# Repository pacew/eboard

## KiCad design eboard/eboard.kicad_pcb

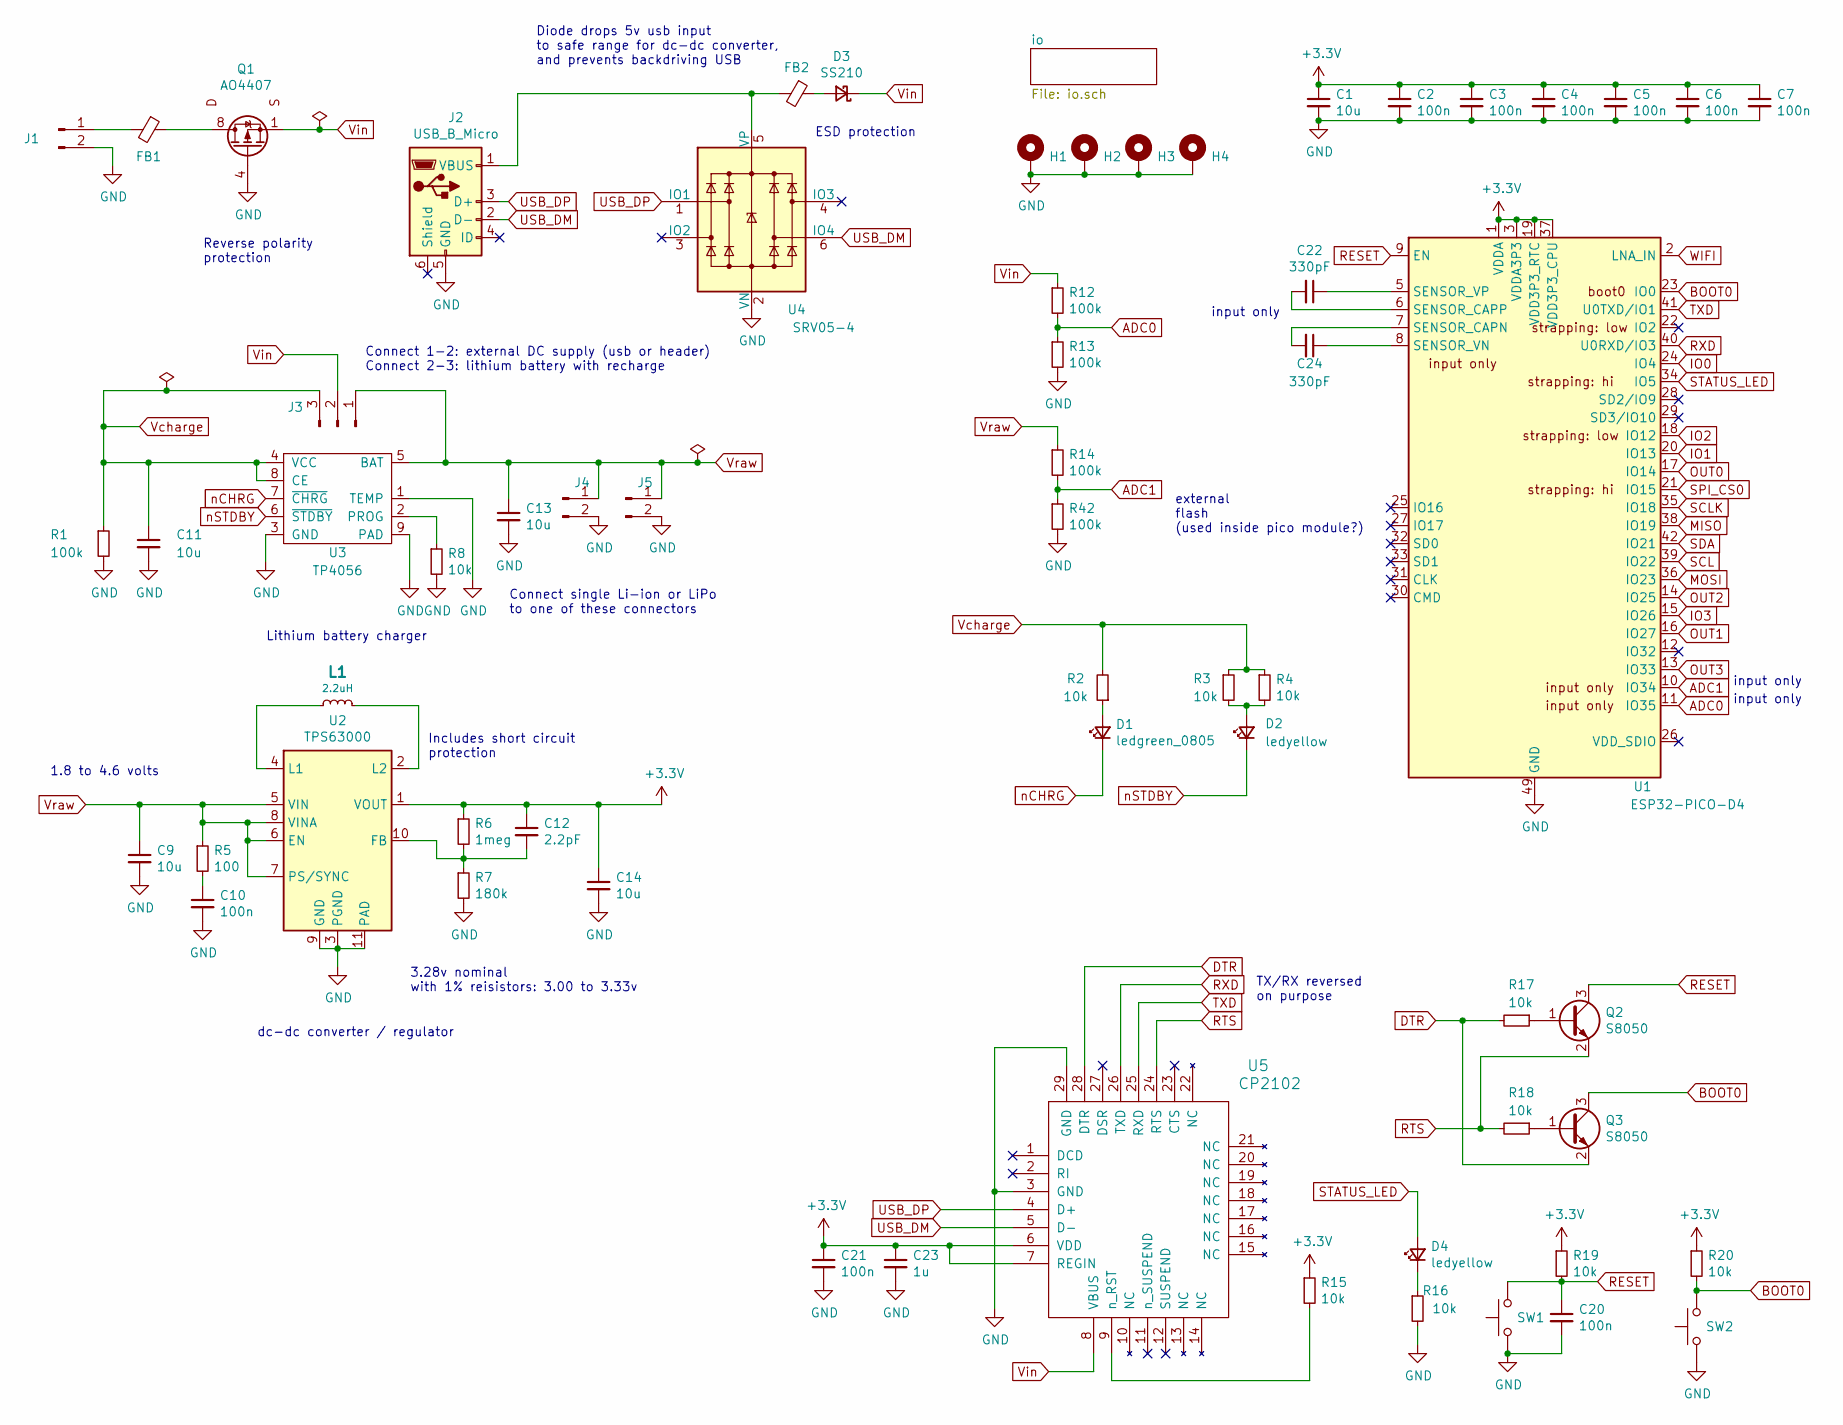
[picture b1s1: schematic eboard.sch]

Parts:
C1, C9, C11, C13, C14: 10u; C_0402_1005Metric; LCSC C15525
C2, C3, C4, C5, C6, C7, C10, C20, C21: 100n; C_0402_1005Metric; LCSC C1525
C12: 2.2pF; C_0402_1005Metric; LCSC C1559
C22, C24: 330pF; C_0402_1005Metric; LCSC C13533
C23: 1u; C_0402_1005Metric; LCSC C52923
D1: ledgreen_0805; LED_0805_2012Metric; LCSC C2297
D2, D4: ledyellow; LED_0603_1608Metric; LCSC C72038
D3: SS210; D_SMA; LCSC C14996
FB1, FB2: bead; L_0805_2012Metric; LCSC C1015
H1, H2, H3, H4: MountingHole_Pad; MountingHole_3.2mm_M3_Pad
J1, J5: Conn_01x02_Male; PinHeader_1x02_P2.54mm_Vertical
J2: USB_B_Micro; USB_Micro-B_Molex-105017-0001
J3: Conn_01x03_Male; PinHeader_1x03_P2.54mm_Vertical
J4: jst_battery; JST_PH_B2B-PH-K_1x02_P2.00mm_Vertical
L1: 2.2uH; L_Coilcraft_XxL4020; LCSC C167747
Q1: AO4407; SOIC-8_3.9x4.9mm_P1.27mm; LCSC C469397
Q2, Q3: S8050; SOT-23; LCSC C2146
R1, R12, R13, R14, R42: 100k; R_0402_1005Metric; LCSC C25741
R2, R3, R4, R8, R15, R16, R17, R18, R19, R20: 10k; R_0402_1005Metric; LCSC C25744
R5: 100; R_0402_1005Metric; LCSC C25076
R6: 1meg; R_0603_1608Metric; LCSC C22935
R7: 180k; R_0603_1608Metric; LCSC C22827
SW1, SW2: pushbutton_switch; SW_PUSH_6mm
U1: ESP32-PICO-D4; QFN-48-1EP_7x7mm_P0.5mm_EP5.3x5.3mm; LCSC C193707
U2: TPS63000; Texas_DRC0010J_ThermalVias; LCSC C24966
U3: TP4056; SOIC-8-1EP_3.9x4.9mm_P1.27mm_EP2.29x3mm_ThermalVias; LCSC C16581
U4: SRV05-4; SOT-23-6; LCSC C85364
U5: CP2102; QFN-28-1EP_5x5mm_P0.5mm_EP3.35x3.35mm_ThermalVias; LCSC C6568

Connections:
+3V3: C1.1, C2.1, C3.1, C4.1, C5.1, C6.1, C7.1, C12.1, C14.1, C21.1, C23.1, R6.1, R15.1, R19.1, R20.1, U1.1 (VDDA), U1.3 (VDDA3P3), U1.4 (VDDA3P3), U1.19 (VDD3P3_RTC), U1.37 (VDD3P3_CPU), U1.43 (VDDA), U1.46 (VDDA), U2.1 (VOUT), U5.6 (VDD), U5.7 (REGIN); also elsewhere on the board
ADC0: R12.2, R13.1, U1.11 (IO35)
ADC1: R14.2, R42.1, U1.10 (IO34)
BOOT0: Q3.3 (C), R20.2, SW2.2, U1.23 (IO0)
DTR: Q3.2 (E), R17.2, U5.28 (DTR)
GND: C1.2, C2.2, C3.2, C4.2, C5.2, C6.2, C7.2, C9.2, C10.2, C11.2, C13.2, C14.2, C20.2, C21.2, C23.2, H1.1, H2.1, H3.1, H4.1, J1.2, J2.5 (GND), J4.2, J5.2, Q1.4 (G), R1.2, R7.2, R8.2, R13.2, R16.2, R42.2, SW1.1, SW2.1, U1.49 (GND), U2.3 (PGND), U2.9 (GND), U2.11 (PAD), U3.1 (TEMP), U3.3 (GND), U3.9 (PAD), U4.2 (VN), U5.3 (GND), U5.29 (GND); also elsewhere on the board
IO0: U1.24 (IO4); also elsewhere on the board
IO1: U1.20 (IO13); also elsewhere on the board
IO2: U1.18 (IO12); also elsewhere on the board
IO3: U1.15 (IO26); also elsewhere on the board
MISO: U1.38 (IO19); also elsewhere on the board
MOSI: U1.36 (IO23); also elsewhere on the board
unnamed: C10.1, R5.2
unnamed: C12.2, R6.2, R7.1, U2.10 (FB)
unnamed: C22.1, U1.5 (SENSOR_VP)
unnamed: C22.2, U1.6 (SENSOR_CAPP)
unnamed: C24.1, U1.8 (SENSOR_VN)
unnamed: C24.2, U1.7 (SENSOR_CAPN)
unnamed: D1.2 (A), R2.1
unnamed: D2.2 (A), R3.2, R4.2
unnamed: D3.2 (A), FB2.1
unnamed: D4.1 (K), R16.1
unnamed: FB1.1, Q1.5 (Dd), Q1.6 (Dc), Q1.7 (Db), Q1.8 (D)
unnamed: FB1.2, J1.1
unnamed: FB2.2, J2.1 (VBUS), U4.5 (VP)
unnamed: L1.1, U2.4 (L1)
unnamed: L1.2, U2.2 (L2)
unnamed: Q2.1 (B), R17.1
unnamed: Q3.1 (B), R18.1
unnamed: R8.1, U3.2 (PROG)
unnamed: R15.2, U5.9 (n_RST)
OUT0: U1.17 (IO14); also elsewhere on the board
OUT1: U1.16 (IO27); also elsewhere on the board
OUT2: U1.14 (IO25); also elsewhere on the board
OUT3: U1.13 (IO33); also elsewhere on the board
RESET: C20.1, Q2.3 (C), R19.2, SW1.2, U1.9 (EN)
RTS: Q2.2 (E), R18.2, U5.24 (RTS)
RXD: U1.40 (U0RXD/IO3), U5.26 (TXD)
SCL: U1.39 (IO22); also elsewhere on the board
SCLK: U1.35 (IO18); also elsewhere on the board
SDA: U1.42 (IO21); also elsewhere on the board
SPI_CS0: U1.21 (IO15); also elsewhere on the board
STATUS_LED: D4.2 (A), U1.34 (IO5)
TXD: U1.41 (U0TXD/IO1), U5.25 (RXD)
USB_DM: J2.2 (D-), U4.6 (IO4), U5.5 (D-)
USB_DP: J2.3 (D+), U4.1 (IO1), U5.4 (D+)
Vcharge: C11.1, J3.3, R1.1, R2.2, R3.1, R4.1, U3.4 (VCC), U3.8 (CE)
Vin: D3.1 (K), J3.2, Q1.1 (S), Q1.2 (Sb), Q1.3 (Sc), R12.1, U5.8 (VBUS)
Vraw: C9.1, C13.1, J3.1, J4.1, J5.1, R5.1, R14.1, U2.5 (VIN), U2.6 (EN), U2.7 (PS/SYNC), U2.8 (VINA), U3.5 (BAT)
WIFI: U1.2 (LNA_IN); also elsewhere on the board
nCHRG: D1.1 (K), U3.7 (~CHRG)
nSTDBY: D2.1 (K), U3.6 (~STDBY)

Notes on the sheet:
3.28v nominal with 1% reisistors: 3.00 to 3.33v
Includes short circuit protection
1.8 to 4.6 volts
Reverse polarity protection
ESD protection
Lithium battery charger
dc-dc converter / regulator
Connect 1-2: external DC supply (usb or header) Connect 2-3: lithium battery with recharge
Connect single Li-ion or LiPo to one of these connectors
external flash (used inside pico module?)
input only
Diode drops 5v usb input to safe range for dc-dc converter, and prevents backdriving USB
TX/RX reversed on purpose

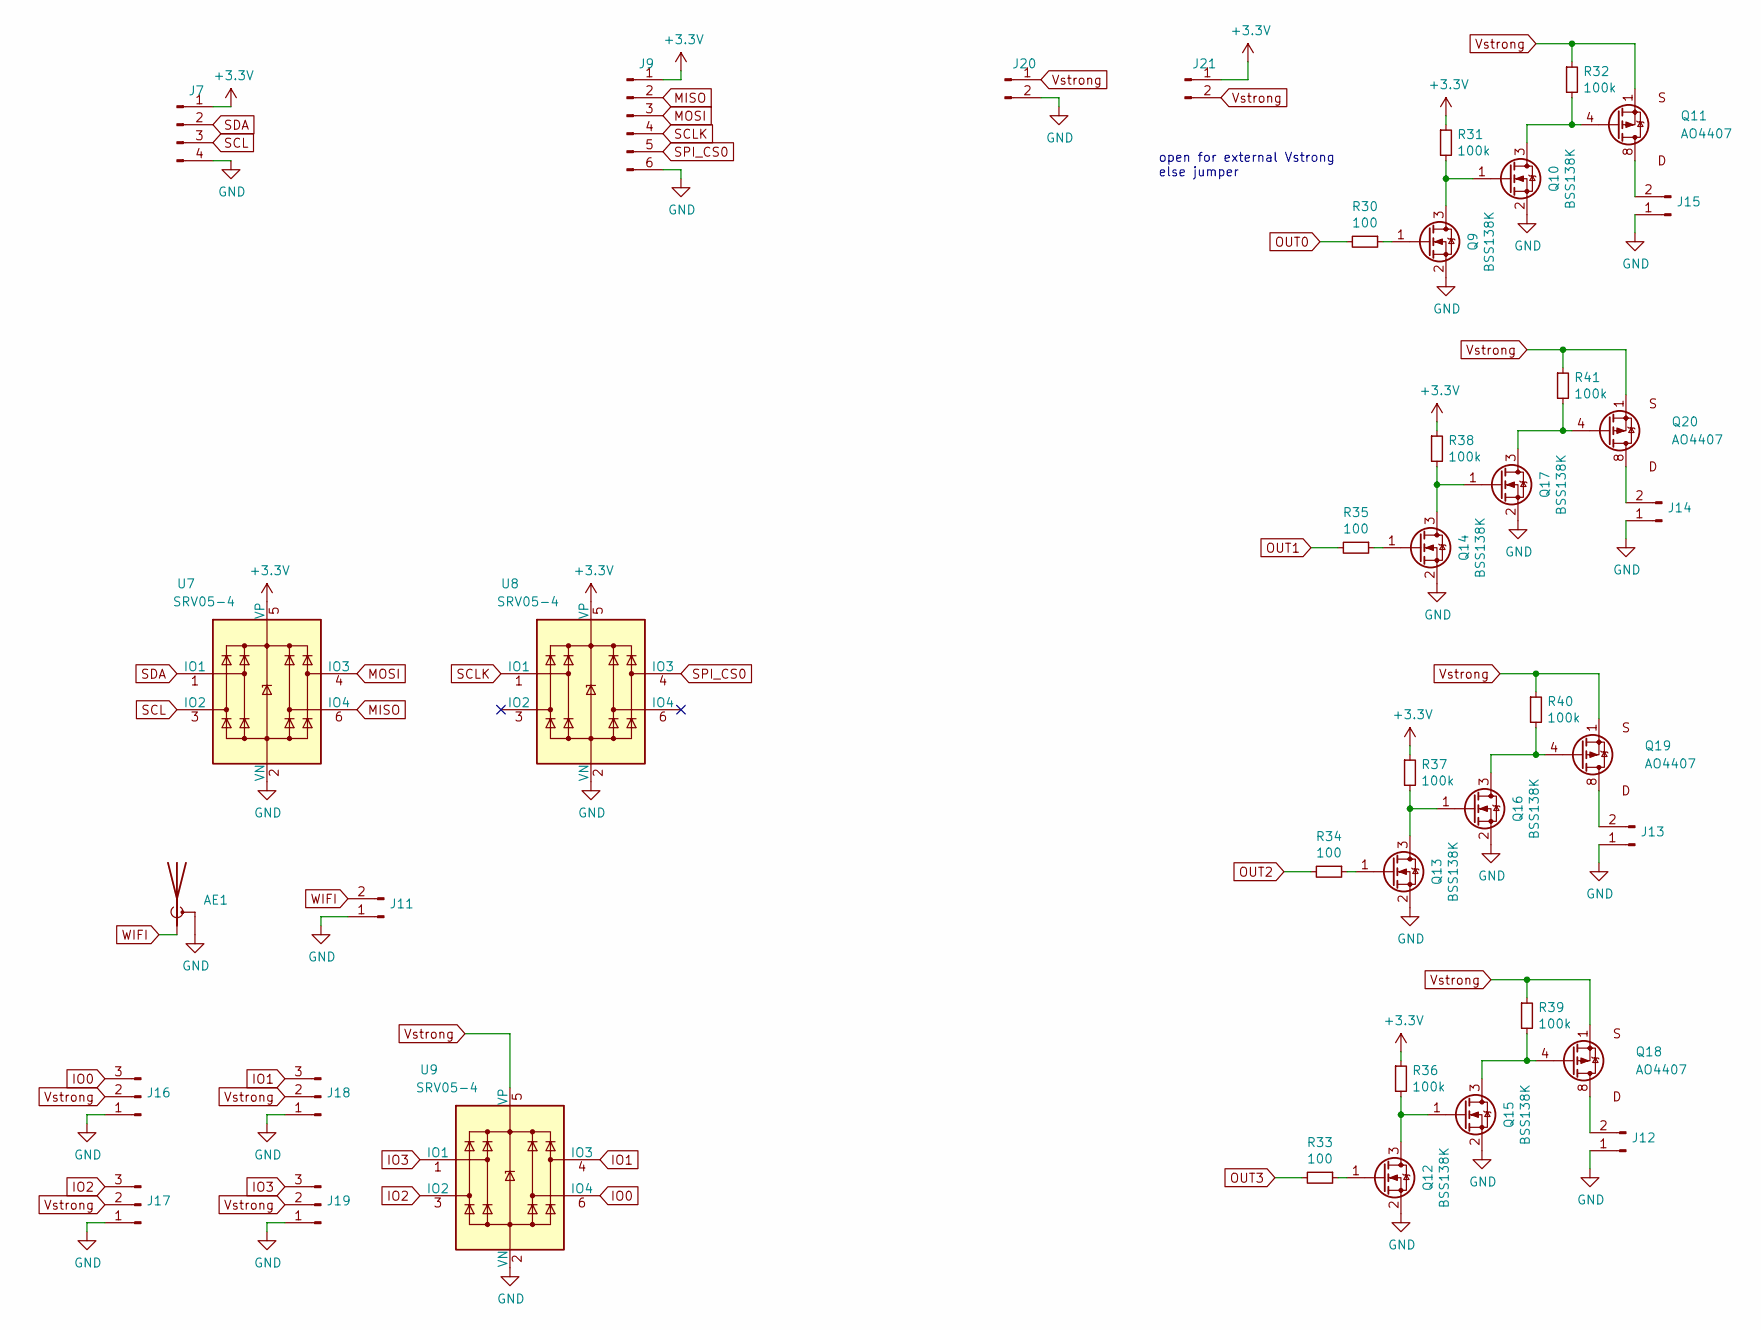
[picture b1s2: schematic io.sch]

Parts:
AE1: Antenna_Shield; SMA_Samtec_SMA-J-P-X-ST-EM1_EdgeMount
J7: Conn_01x04_Male; PinHeader_1x04_P2.54mm_Vertical
J9: Conn_01x06_Male; PinHeader_1x06_P2.54mm_Vertical
J11, J12, J13, J14, J15, J20, J21: Conn_01x02_Male; PinHeader_1x02_P2.54mm_Vertical
J16, J17, J18, J19: Conn_01x03_Male; PinHeader_1x03_P2.54mm_Vertical
Q9, Q10, Q12, Q13, Q14, Q15, Q16, Q17: BSS138K; SOT-23; LCSC C255592
Q11, Q18, Q19, Q20: AO4407; SOIC-8_3.9x4.9mm_P1.27mm; LCSC C469397
R30, R33, R34, R35: 100; R_0402_1005Metric; LCSC C25076
R31, R32, R36, R37, R38, R39, R40, R41: 100k; R_0402_1005Metric; LCSC C25741
U7, U8, U9: SRV05-4; SOT-23-6; LCSC C85364

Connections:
+3V3: J7.1, J9.1, J21.1, R31.1, R36.1, R37.1, R38.1, U7.5 (VP), U8.5 (VP); also elsewhere on the board
GND: AE1.2 (Shield), J7.4, J9.6, J11.1, J12.1, J13.1, J14.1, J15.1, J16.1, J17.1, J18.1, J19.1, J20.2, Q9.2 (S), Q10.2 (S), Q12.2 (S), Q13.2 (S), Q14.2 (S), Q15.2 (S), Q16.2 (S), Q17.2 (S), U7.2 (VN), U8.2 (VN), U9.2 (VN); also elsewhere on the board
IO0: J16.3, U9.6 (IO4); also elsewhere on the board
IO1: J18.3, U9.4 (IO3); also elsewhere on the board
IO2: J17.3, U9.3 (IO2); also elsewhere on the board
IO3: J19.3, U9.1 (IO1); also elsewhere on the board
MISO: J9.2, U7.6 (IO4); also elsewhere on the board
MOSI: J9.3, U7.4 (IO3); also elsewhere on the board
unnamed: J12.2, Q18.5 (Dd), Q18.6 (Dc), Q18.7 (Db), Q18.8 (D)
unnamed: J13.2, Q19.5 (Dd), Q19.6 (Dc), Q19.7 (Db), Q19.8 (D)
unnamed: J14.2, Q20.5 (Dd), Q20.6 (Dc), Q20.7 (Db), Q20.8 (D)
unnamed: J15.2, Q11.5 (Dd), Q11.6 (Dc), Q11.7 (Db), Q11.8 (D)
unnamed: Q9.1 (G), R30.1
unnamed: Q9.3 (D), Q10.1 (G), R31.2
unnamed: Q10.3 (D), Q11.4 (G), R32.2
unnamed: Q12.1 (G), R33.1
unnamed: Q12.3 (D), Q15.1 (G), R36.2
unnamed: Q13.1 (G), R34.1
unnamed: Q13.3 (D), Q16.1 (G), R37.2
unnamed: Q14.1 (G), R35.1
unnamed: Q14.3 (D), Q17.1 (G), R38.2
unnamed: Q15.3 (D), Q18.4 (G), R39.2
unnamed: Q16.3 (D), Q19.4 (G), R40.2
unnamed: Q17.3 (D), Q20.4 (G), R41.2
OUT0: R30.2; also elsewhere on the board
OUT1: R35.2; also elsewhere on the board
OUT2: R34.2; also elsewhere on the board
OUT3: R33.2; also elsewhere on the board
SCL: J7.3, U7.3 (IO2); also elsewhere on the board
SCLK: J9.4, U8.1 (IO1); also elsewhere on the board
SDA: J7.2, U7.1 (IO1); also elsewhere on the board
SPI_CS0: J9.5, U8.4 (IO3); also elsewhere on the board
Vstrong: J16.2, J17.2, J18.2, J19.2, J20.1, J21.2, Q11.1 (S), Q11.2 (Sb), Q11.3 (Sc), Q18.1 (S), Q18.2 (Sb), Q18.3 (Sc), Q19.1 (S), Q19.2 (Sb), Q19.3 (Sc), Q20.1 (S), Q20.2 (Sb), Q20.3 (Sc), R32.1, R39.1, R40.1, R41.1, U9.5 (VP)
WIFI: AE1.1 (A), J11.2; also elsewhere on the board

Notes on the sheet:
open for external Vstrong else jumper

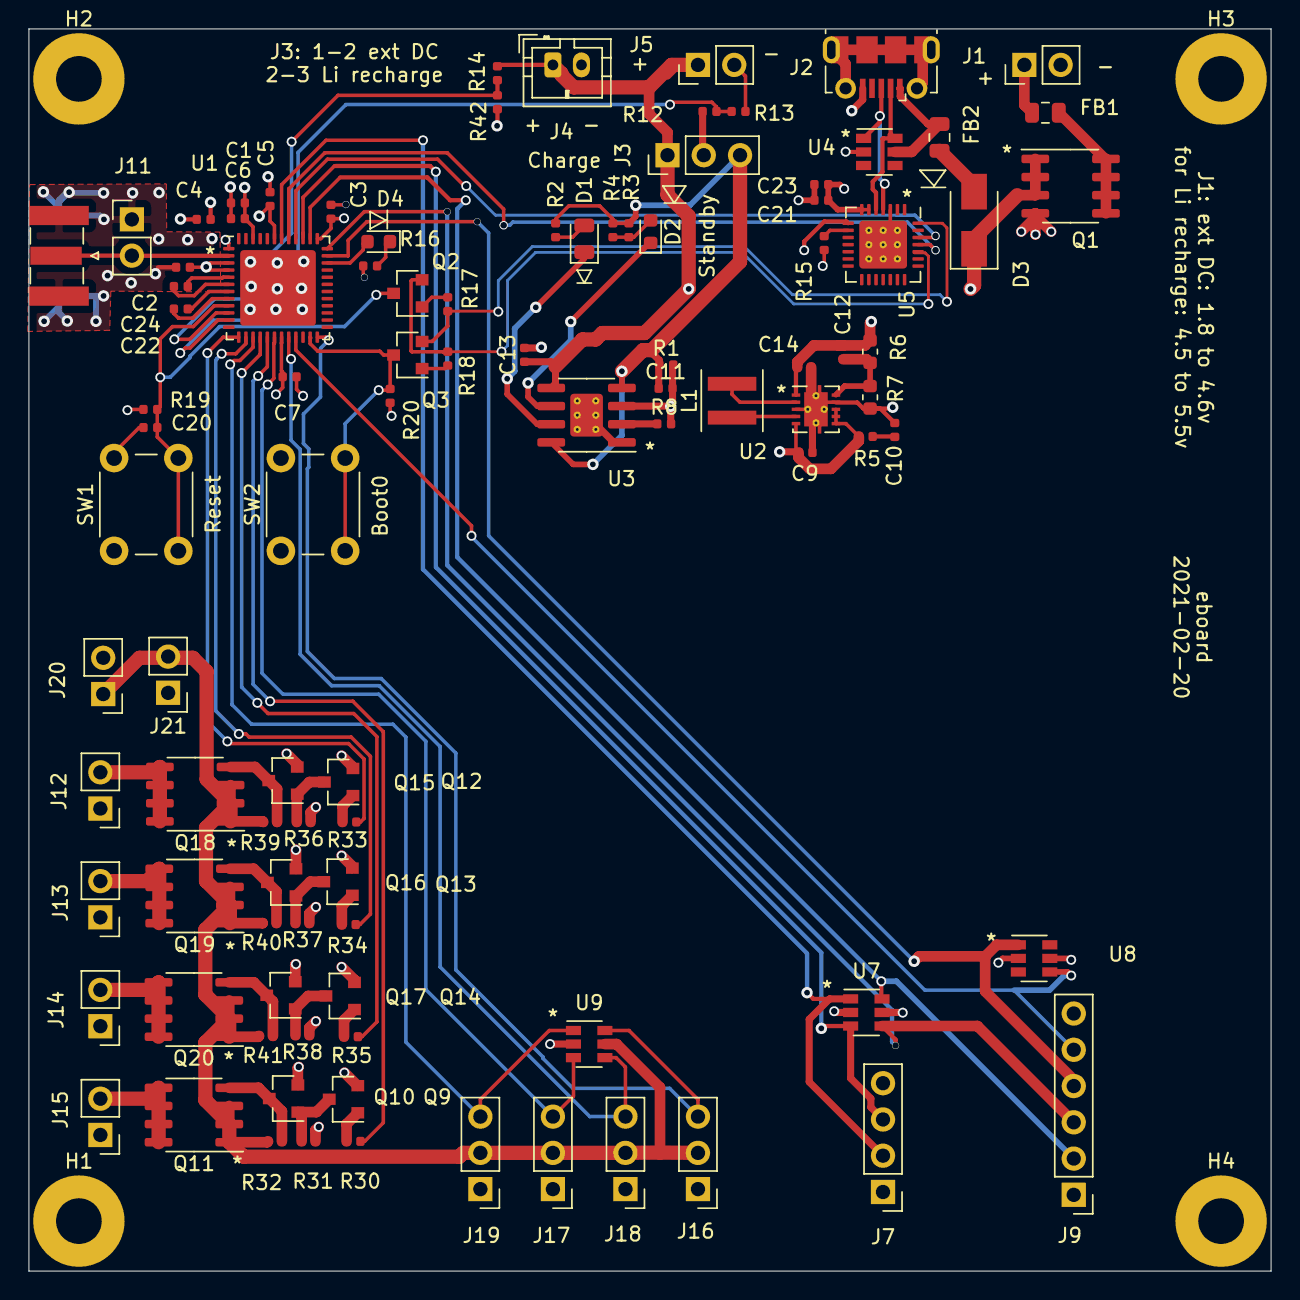
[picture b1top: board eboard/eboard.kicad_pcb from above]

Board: 4 copper layers, 87.0 x 87.0 mm, 103 parts (0 on the bottom side), 69 nets.

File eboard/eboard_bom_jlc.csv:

"Comment","Designator","Footprint","LCSC Part #"
"100n","C10,C7,C6,C5,C4,C3,C2,C20,C21","C_0402_1005Metric","C1525"
"10u","C11,C13,C14,C9,C1","C_0402_1005Metric","C15525"
"2.2pF","C12","C_0402_1005Metric","C1559"
"330pF","C22,C24","C_0402_1005Metric","C13533"
"1u","C23","C_0402_1005Metric","C52923"
"ledgreen","D1,D4","LED_0603_1608Metric","C2297"
"ledyellow","D2","LED_0603_1608Metric","C72038"
"SS210","D3","D_SMA","C14996"
"bead","FB2,FB1","L_0805_2012Metric","C1015"
"2.2uH","L1","L_Coilcraft_XxL4020","C167747"
"AO4407","Q1,Q11,Q20,Q19,Q18","SOIC-8_3.9x4.9mm_P1.27mm","C469397"
"S8050","Q2,Q3","SOT-23","C2146"
"BSS138K","Q10,Q9,Q17,Q14,Q16,Q13,Q15,Q12","SOT-23","C255592"
"100k","R1,R12,R13,R14,R42,R32,R31,R41,R38,R40,R37,R39,R36","R_0402_1005Metric","C25741"
"10k","R2,R8,R4,R3,R16,R20,R19,R15,R17,R18","R_0402_1005Metric","C25744"
"100","R5,R30,R35,R34,R33","R_0402_1005Metric","C25076"
"1meg","R6","R_0603_1608Metric","C22935"
"180k","R7","R_0603_1608Metric","C22827"
"ESP32-PICO-D4","U1","QFN-48-1EP_7x7mm_P0.5mm_EP5.3x5.3mm","C193707"
"TPS63000","U2","Texas_DRC0010J_ThermalVias","C24966"
"TP4056","U3","SOIC-8-1EP_3.9x4.9mm_P1.27mm_EP2.29x3mm_ThermalVias","C16581"
"SRV05-4","U4,U7,U8,U9","SOT-23-6","C85364"
"CP2102","U5","QFN-28-1EP_5x5mm_P0.5mm_EP3.35x3.35mm_ThermalVias","C6568"

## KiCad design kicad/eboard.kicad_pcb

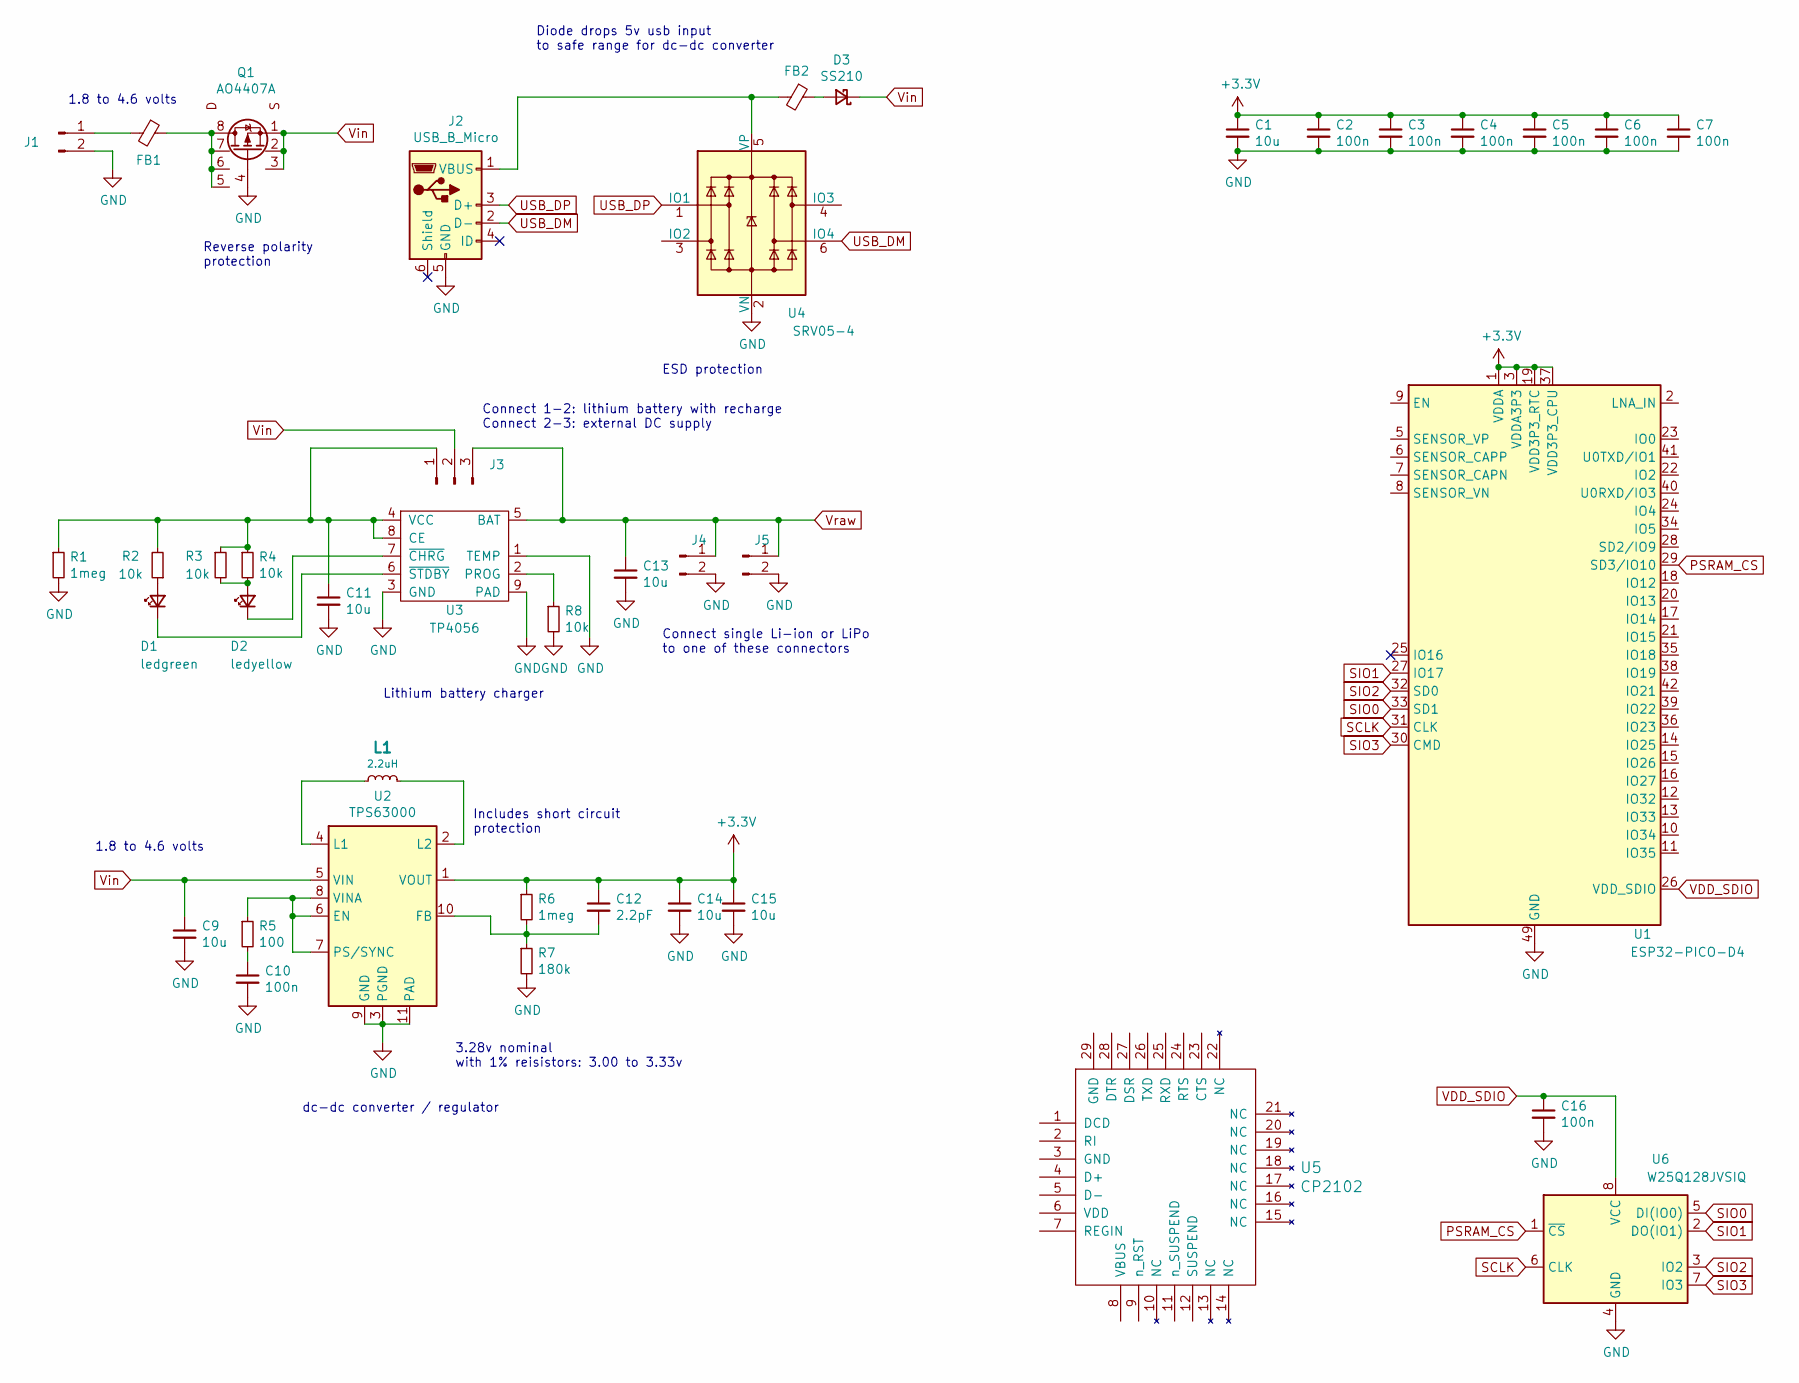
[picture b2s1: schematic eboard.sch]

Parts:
C1, C9, C11, C13, C14, C15: 10u; C_0402_1005Metric; LCSC C15525
C2, C3, C4, C5, C6, C7, C10, C16: 100n; C_0402_1005Metric; LCSC C1525
C12: 2.2pF; C_0402_1005Metric; LCSC C1559
D1: ledgreen; LED_0603_1608Metric; LCSC C2297
D2: ledyellow; LED_0603_1608Metric; LCSC C72038
D3: SS210; D_SMA; LCSC C14996
FB1, FB2: bead; L_0805_2012Metric; LCSC C1015
J1, J4, J5: Conn_01x02_Male; PinHeader_1x02_P2.54mm_Vertical
J2: USB_B_Micro; USB_Micro-B_Molex-105017-0001
J3: Conn_01x03_Male; PinHeader_1x03_P2.54mm_Vertical
L1: 2.2uH; L_Coilcraft_XxL4020; LCSC C167747
Q1: AO4407A; SOIC-8_3.9x4.9mm_P1.27mm; LCSC C16072
R1, R6: 1meg; R_0603_1608Metric; LCSC C22935
R2, R3, R4, R8: 10k; R_0402_1005Metric; LCSC C25744
R5: 100; R_0402_1005Metric; LCSC C25076
R7: 180k; R_0603_1608Metric; LCSC C22827
U1: ESP32-PICO-D4; QFN-48-1EP_7x7mm_P0.5mm_EP5.3x5.3mm; LCSC C193707
U2: TPS63000; Texas_DRC0010J_ThermalVias
U3: TP4056; SOIC-8-1EP_3.9x4.9mm_P1.27mm_EP2.29x3mm_ThermalVias; LCSC C16581
U4: SRV05-4; SOT-23-6; LCSC C85364
U5: CP2102; QFN-28-1EP_5x5mm_P0.5mm_EP3.35x3.35mm_ThermalVias; LCSC C6568
U6: W25Q128JVSIQ; SOIC-8_5.23x5.23mm_P1.27mm; LCSC C97521

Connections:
+3V3: C1.1, C2.1, C3.1, C4.1, C5.1, C6.1, C7.1, C12.1, C14.1, C15.1, R6.1, U1.1 (VDDA), U1.3 (VDDA3P3), U1.4 (VDDA3P3), U1.19 (VDD3P3_RTC), U1.37 (VDD3P3_CPU), U1.43 (VDDA), U1.46 (VDDA), U2.1 (VOUT)
GND: C1.2, C2.2, C3.2, C4.2, C5.2, C6.2, C7.2, C9.2, C10.2, C11.2, C13.2, C14.2, C15.2, C16.2, J1.2, J2.5 (GND), J4.2, J5.2, Q1.4 (G), R1.2, R7.2, R8.2, U1.49 (GND), U2.3 (PGND), U2.9 (GND), U2.11 (PAD), U3.1 (TEMP), U3.3 (GND), U3.9 (PAD), U4.2 (VN), U6.4 (GND)
unnamed: C10.1, R5.2
unnamed: C11.1, J3.1, R1.1, R2.2, R3.1, R4.1, U3.4 (VCC), U3.8 (CE)
unnamed: C12.2, R6.2, R7.1, U2.10 (FB)
unnamed: D1.1 (K), U3.6 (~STDBY)
unnamed: D1.2 (A), R2.1
unnamed: D2.1 (K), U3.7 (~CHRG)
unnamed: D2.2 (A), R3.2, R4.2
unnamed: D3.2 (A), FB2.1
unnamed: FB1.1, Q1.5 (Dd), Q1.6 (Dc), Q1.7 (Db), Q1.8 (D)
unnamed: FB1.2, J1.1
unnamed: FB2.2, J2.1 (VBUS), U4.5 (VP)
unnamed: L1.1, U2.4 (L1)
unnamed: L1.2, U2.2 (L2)
unnamed: R5.1, U2.6 (EN), U2.7 (PS/SYNC), U2.8 (VINA)
unnamed: R8.1, U3.2 (PROG)
PSRAM_CS: U1.29 (SD3/IO10), U6.1 (~CS)
SCLK: U1.31 (CLK), U6.6 (CLK)
SIO0: U1.33 (SD1), U6.5 (DI(IO0))
SIO1: U1.27 (IO17), U6.2 (DO(IO1))
SIO2: U1.32 (SD0), U6.3 (IO2)
SIO3: U1.30 (CMD), U6.7 (IO3)
USB_DM: J2.2 (D-), U4.6 (IO4)
USB_DP: J2.3 (D+), U4.1 (IO1)
VDD_SDIO: C16.1, U1.26 (VDD_SDIO), U6.8 (VCC)
Vin: C9.1, D3.1 (K), J3.2, Q1.1 (S), Q1.2 (Sb), Q1.3 (Sc), U2.5 (VIN)
Vraw: C13.1, J3.3, J4.1, J5.1, U3.5 (BAT)

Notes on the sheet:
1.8 to 4.6 volts
3.28v nominal with 1% reisistors: 3.00 to 3.33v
Includes short circuit protection
Reverse polarity protection
ESD protection
Lithium battery charger
dc-dc converter / regulator
Connect 1-2: lithium battery with recharge Connect 2-3: external DC supply
Connect single Li-ion or LiPo to one of these connectors
Diode drops 5v usb input to safe range for dc-dc converter

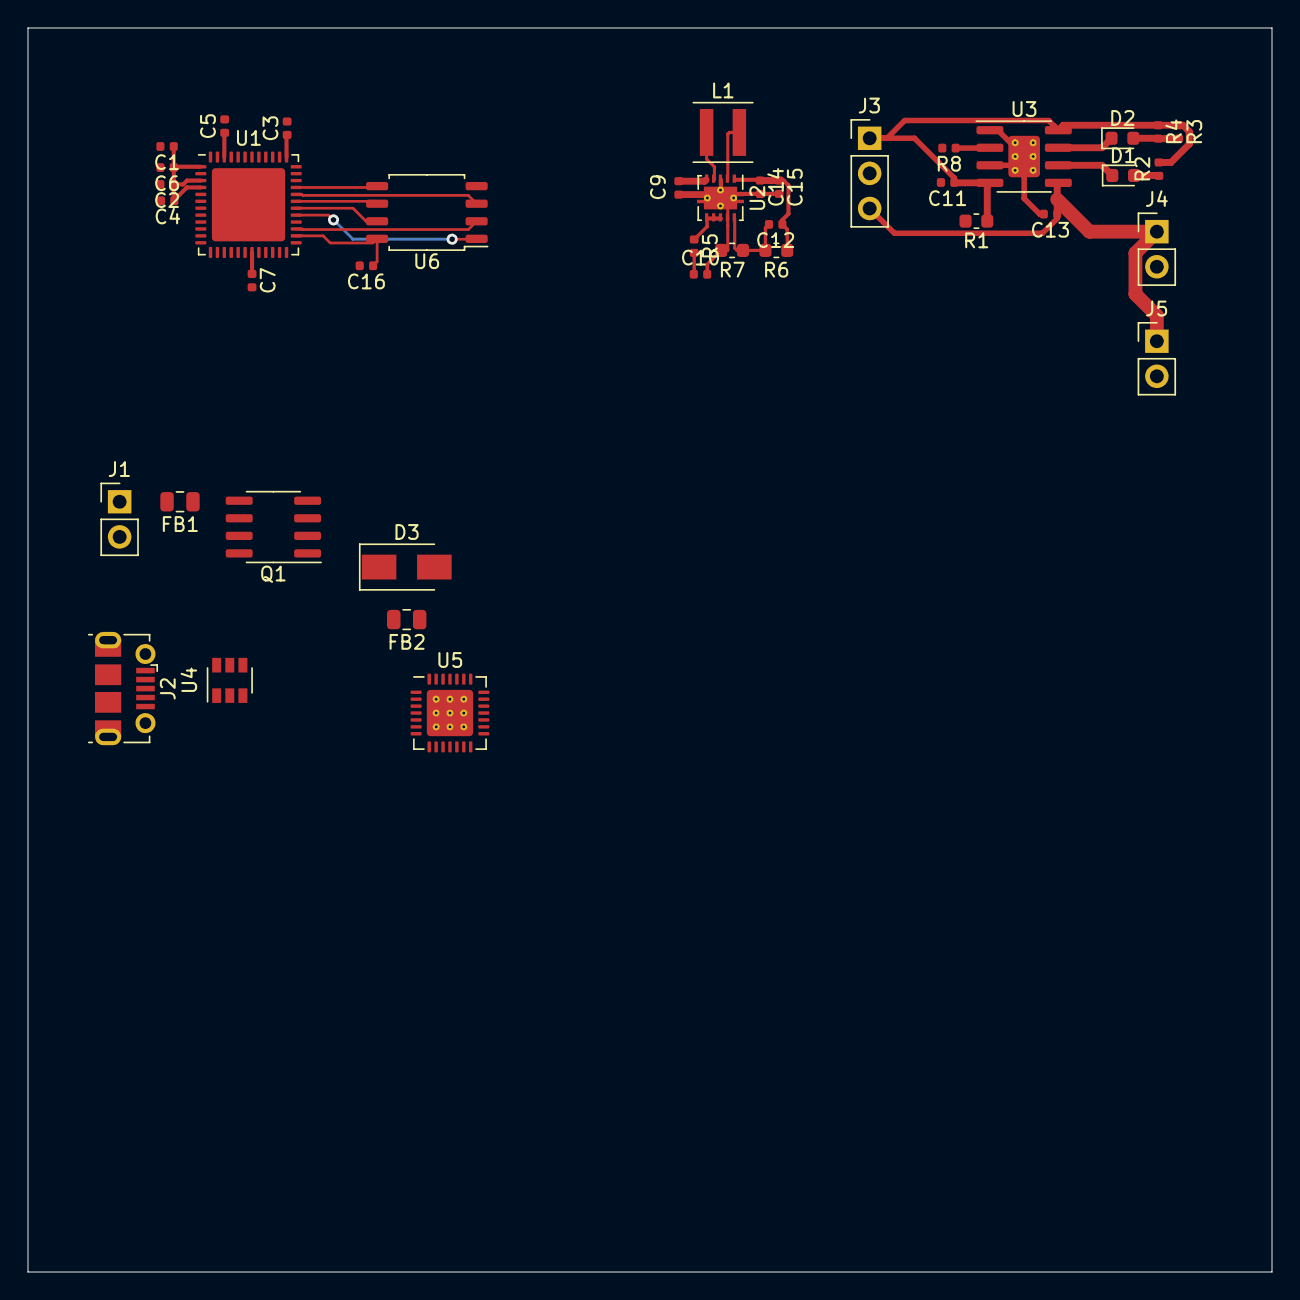
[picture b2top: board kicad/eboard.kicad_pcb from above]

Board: 4 copper layers, 90.0 x 90.0 mm, 41 parts (0 on the bottom side), 28 nets.

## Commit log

2020-10-31 start
2020-11-01 sim2
2020-11-02 dcdc
2020-11-07 docs
2020-11-08 power
2020-11-09 cleanup
2020-11-10 rename
2020-11-10 makefile
2020-11-10 progress
2020-12-06 routing
2020-12-06 routed
2020-12-07 manf
2020-12-07 silkscreen
2020-12-07 fab2
2020-12-07 fab3
2020-12-07 fab4
2020-12-27 rescue
2020-12-28 ecos from v1
2020-12-28 remove 5v
2021-02-27 leds
2021-03-05 python
2021-03-05 sermon
2021-03-05 website
2021-03-06 reload
2021-03-06 remove cfg.json
2021-03-06 curses
2021-03-06 vals
